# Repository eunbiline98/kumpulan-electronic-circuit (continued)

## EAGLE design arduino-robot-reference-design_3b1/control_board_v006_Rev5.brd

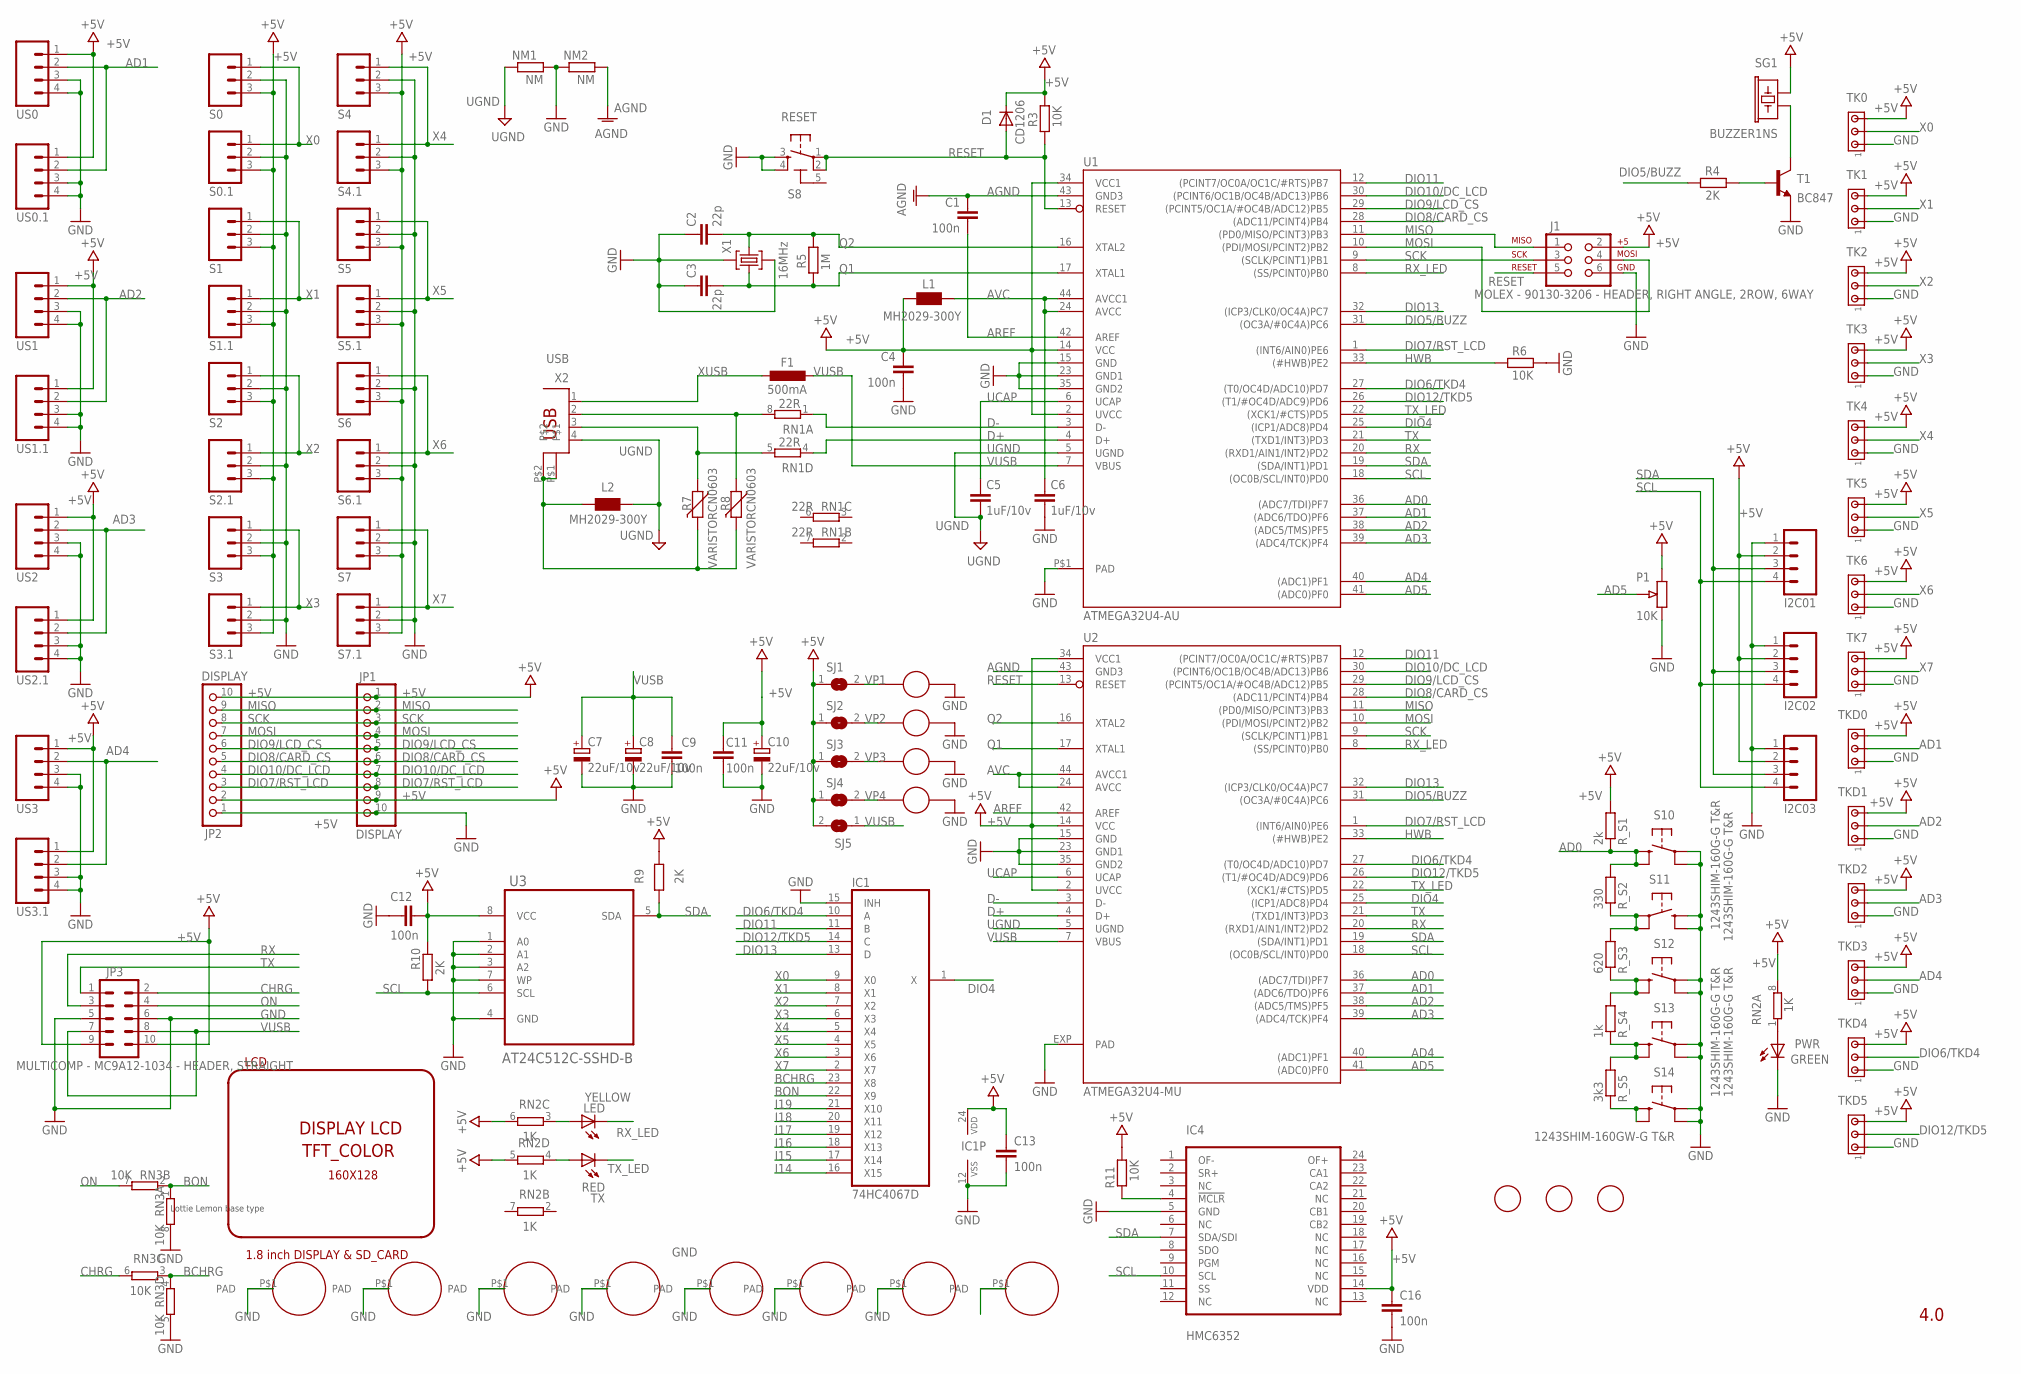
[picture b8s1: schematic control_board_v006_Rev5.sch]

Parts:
1, 2, 3: FIDUCIALMOUNT; FIDUCIA-MOUNT
C1, C4, C9, C11, C12, C13, C16: 100n; C0603-ROUND
C2, C3: 22p; C0603-ROUND
C5, C6: 1uF/10v; C0603-ROUND
C7, C8, C10: 22uF/10v; SMC_B
D1: CD1206; MINIMELF
F1: 500mA; L1812
G1: LOTTIE_LEMON_BASE_TYPE; BASE_ROBOT_001
H1, H2, H3, H4, H5, H6, H7, H8: 2.5-MOUNTING-HOLE; 2.5PAD
I2C01, I2C02, I2C03: M04PTH; 1X04
IC1: 74HC4067D; SO24W
IC4: HMC6352
J1: MOLEX - 90130-3206 - HEADER, RIGHT ANGLE, 2ROW, 6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; 2X3
JP1, JP2: DISPLAY; 1X10-TH
JP3: MULTICOMP - MC9A12-1034 - HEADER, STRAIGHT; 2X5-SHROUDED_LOCK
L1, L2: MH2029-300Y; 0805
LCD: 1.8 inch DISPLAY & SD_CARD; 1.8-LCD
LED: YELLOW; CHIP-LED0805
NM1, NM2: NM; R0805
P1: 10K; POT-V
PTZ1, PTZ2: LOTTIE_LEMON_PADS_SUP; PADS_LOTTIE_LEMON_SUP
PTZ3, PTZ4: LOTTIE_LEMON_PADS_SUP1; PADS_LOTTIE_LEMON_SUP
PWR: LEDCHIP-LED0805; CHIP-LED0805
R3, R6, R11: 10K; R0603-ROUND
R4, R9, R10: 2K; R0603-ROUND
R5: 1M; R0603-ROUND
R7, R8: VARISTORCN0603; CT/CN0603
RN1: 22R; CAY16
RN2: 1K; CAY16
RN3: 10K; CAY16
R_S1: 2k; R0603-ROUND
R_S2: 330; R0603-ROUND
R_S3: 620; R0603-ROUND
R_S4: 1k; R0603-ROUND
R_S5: 3k3; R0603-ROUND
S0, S0.1, S1, S1.1, S2, S2.1, S3, S3.1, S4, S4.1, S5, S5.1, S6, S6.1, S7, S7.1: M03PTH; 1X03
S8: RESET; TS42
S10, S11, S12, S13: 1243SHIM-160G-G T&R; TACTILE-SMD-12MM
S14: 1243SHIM-160GW-G T&R; TACTILE-SMD-12MM
SG1: BUZZER1NS; BUZZER-12MM-NS
SJ1, SJ2, SJ3, SJ4: SJ
SJ5: SJL
T1: BC847; SOT23
TK0, TK1, TK2, TK3, TK4, TK5, TK6, TK7: MTA03-100; 10X03MTA
TKD0, TKD1, TKD2, TKD3, TKD4, TKD5: MTA03-100; 10X03MTA
TX: RED; CHIP-LED0805
U1: ATMEGA32U4-AU; TQFP44-PAD
U2: ATMEGA32U4-MU; QFN44ML7X7
U3: AT24C512C-SSHD-B; SOIC127P600X175-8N
US0, US0.1, US1, US1.1, US2, US2.1, US3, US3.1: M04PTH; 1X04
X1: 16MHz; CRYSTAL-3.2-2.5
X2: USB; PN61729

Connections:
5-GND: S8.5 (5-GND)
+5V: C4.1, C10.+, C11.1, C12.1, C13.1, C16.1, D1.C, I2C01.2, I2C02.2, I2C03.2, IC1.24 (VDD), IC4.14 (VDD), J1.2, JP1.1, JP1.9, JP2.2, JP2.10, JP3.9, JP3.10, L1.2, P1.B, R3.1, R9.2, R10.1, R11.1, RN2.5 (2), RN2.6 (2), RN2.8 (2), R_S1.2, S0.3, S0.1.3, S1.3, S1.1.3, S2.3, S2.1.3, S3.3, S3.1.3, S4.3, S4.1.3, S5.3, S5.1.3, S6.3, S6.1.3, S7.3, S7.1.3, SG1.+ (1), SJ1.1, SJ2.1, SJ3.1, SJ4.1, SJ5.2, TK0.3, TK1.3, TK2.3, TK3.3, TK4.3, TK5.3, TK6.3, TK7.3, TKD0.3, TKD1.3, TKD2.3, TKD3.3, TKD4.3, TKD5.3, U1.2 (UVCC), U1.14 (VCC), U1.34 (VCC1), U2.2 (UVCC), U2.14 (VCC), U2.34 (VCC1), U3.8 (VCC), US0.1, US0.1.1, US1.1, US1.1.1, US2.1, US2.1.1, US3.1, US3.1.1
AD0: R_S1.1, R_S2.2, S10.P$3 (3), S10.P$4 (4), U1.36 ((ADC7/TDI)PF7), U2.36 ((ADC7/TDI)PF7)
AD1: TKD0.2, U1.37 ((ADC6/TDO)PF6), U2.37 ((ADC6/TDO)PF6), US0.2, US0.1.2
AD2: TKD1.2, U1.38 ((ADC5/TMS)PF5), U2.38 ((ADC5/TMS)PF5), US1.2, US1.1.2
AD3: TKD2.2, U1.39 ((ADC4/TCK)PF4), U2.39 ((ADC4/TCK)PF4), US2.2, US2.1.2
AD4: TKD3.2, U1.40 ((ADC1)PF1), U2.40 ((ADC1)PF1), US3.2, US3.1.2
AD5: P1.C, U1.41 ((ADC0)PF0), U2.41 ((ADC0)PF0)
AGND: C1.1, NM2.1, U1.43 (GND3), U2.43 (GND3)
AREF: C1.2, U1.42 (AREF), U2.42 (AREF)
AVC: C6.1, L1.1, U1.24 (AVCC), U1.44 (AVCC1), U2.24 (AVCC), U2.44 (AVCC1)
BCHRG: IC1.23 (X8), RN3.3 (1), RN3.4 (1)
BON: IC1.22 (X9), RN3.1, RN3.2 (1)
CHRG: JP3.2, RN3.6 (2)
D+: RN1.4 (1), U1.4 (D+), U2.4 (D+)
D-: RN1.1, U1.3 (D-), U2.3 (D-)
DIO4: IC1.1 (X), U1.25 ((ICP1/ADC8)PD4), U2.25 ((ICP1/ADC8)PD4)
DIO5/BUZZ: R4.2, U1.31 ((OC3A/#0C4A)PC6), U2.31 ((OC3A/#0C4A)PC6)
DIO6/TKD4: IC1.10 (A), TKD4.2, U1.27 ((T0/OC4D/ADC10)PD7), U2.27 ((T0/OC4D/ADC10)PD7)
DIO7/RST_LCD: JP1.8, JP2.3, U1.1 ((INT6/AIN0)PE6), U2.1 ((INT6/AIN0)PE6)
DIO8/CARD_CS: JP1.6, JP2.5, U1.28 ((ADC11/PCINT4)PB4), U2.28 ((ADC11/PCINT4)PB4)
DIO9/LCD_CS: JP1.5, JP2.6, U1.29 ((PCINT5/OC1A/#OC4B/ADC12)PB5), U2.29 ((PCINT5/OC1A/#OC4B/ADC12)PB5)
DIO10/DC_LCD: JP1.7, JP2.4, U1.30 ((PCINT6/OC1B/OC4B/ADC13)PB6), U2.30 ((PCINT6/OC1B/OC4B/ADC13)PB6)
DIO11: IC1.11 (B), U1.12 ((PCINT7/OC0A/OC1C/#RTS)PB7), U2.12 ((PCINT7/OC0A/OC1C/#RTS)PB7)
DIO12/TKD5: IC1.14 (C), TKD5.2, U1.26 ((T1/#OC4D/ADC9)PD6), U2.26 ((T1/#OC4D/ADC9)PD6)
DIO13: IC1.13 (D), U1.32 ((ICP3/CLK0/OC4A)PC7), U2.32 ((ICP3/CLK0/OC4A)PC7)
GND: C2.1, C3.1, C4.2, C6.2, C7.-, C8.-, C9.2, C10.-, C11.2, C12.2, C13.2, C16.2, H1.P$1, H2.P$1, H3.P$1, H4.P$1, H5.P$1, H6.P$1, H7.P$1, H8.P$1, I2C01.1, I2C02.1, I2C03.1, IC1.12 (VSS), IC1.15 (INH), IC4.5 (GND), J1.6, JP1.10, JP2.1, JP3.5, JP3.6, NM1.1, NM2.2, P1.A, PTZ1.P$52 (2), PTZ2.P$52 (2), PTZ3.P$52 (2), PTZ4.P$52 (2), PWR.C, R6.1, RN3.5 (2), RN3.8 (2), S0.2, S0.1.2, S1.2, S1.1.2, S2.2, S2.1.2, S3.2, S3.1.2, S4.2, S4.1.2, S5.2, S5.1.2, S6.2, S6.1.2, S7.2, S7.1.2, S8.3, S8.4, S10.P$1 (1), S10.P$2 (2), S11.P$3 (3), S11.P$4 (4), S12.P$1 (1), S12.P$2 (2), S13.P$1 (1), S13.P$2 (2), S14.P$1 (1), S14.P$2 (2), T1.2 (E), TK0.1, TK1.1, TK2.1, TK3.1, TK4.1, TK5.1, TK6.1, TK7.1, TKD0.1, TKD1.1, TKD2.1, TKD3.1, TKD4.1, TKD5.1, U1.15 (GND), U1.23 (GND1), U1.35 (GND2), U1.P$1 (PAD), U2.15 (GND), U2.23 (GND1), U2.35 (GND2), U2.EXP (PAD), U3.1 (A0), U3.2 (A1), U3.3 (A2), U3.4 (GND), U3.7 (WP), US0.3, US0.4, US0.1.3, US0.1.4, US1.3, US1.4, US1.1.3, US1.1.4, US2.3, US2.4, US2.1.3, US2.1.4, US3.3, US3.4, US3.1.3, US3.1.4, X1.2 (GND), X1.4 (GND)
HWB: R6.2, U1.33 ((#HWB)PE2), U2.33 ((#HWB)PE2)
I14: IC1.16 (X15)
I15: IC1.17 (X14)
I16: IC1.18 (X13)
I17: IC1.19 (X12)
I18: IC1.20 (X11)
I19: IC1.21 (X10)
MISO: J1.1, JP1.2, JP2.9, U1.11 ((PD0/MISO/PCINT3)PB3), U2.11 ((PD0/MISO/PCINT3)PB3)
MOSI: J1.4, JP1.4, JP2.7, U1.10 ((PDI/MOSI/PCINT2)PB2), U2.10 ((PDI/MOSI/PCINT2)PB2)
unnamed: R8.1, RN1.8 (2), X2.2
unnamed: R7.1, RN1.5 (2), X2.3
unnamed: RN2.4 (1), TX.A
unnamed: IC4.4 (!MCLR), R11.2
unnamed: L2.1, R7.2, R8.2, X2.P$1, X2.P$2
unnamed: R_S2.1, R_S3.2, S11.P$1 (1), S11.P$2 (2)
unnamed: LED.A, RN2.3 (1)
unnamed: SG1.- (2), T1.3 (C)
unnamed: PWR.A, RN2.1
unnamed: R_S3.1, R_S4.2, S12.P$3 (3), S12.P$4 (4)
unnamed: R_S4.1, R_S5.2, S13.P$3 (3), S13.P$4 (4)
unnamed: R_S5.1, S14.P$3 (3), S14.P$4 (4)
unnamed: R4.1, T1.1 (B)
ON: JP3.4, RN3.7 (2)
Q1: C3.2, R5.2, U1.17 (XTAL1), U2.17 (XTAL1), X1.1 (C1)
Q2: C2.2, R5.1, U1.16 (XTAL2), U2.16 (XTAL2), X1.3 (C2)
RESET: D1.A, J1.5, R3.2, S8.1, S8.2, U1.13 (RESET), U2.13 (RESET)
RX: JP3.3, U1.20 ((RXD1/AIN1/INT2)PD2), U2.20 ((RXD1/AIN1/INT2)PD2)
RX_LED: LED.C, U1.8 ((SS/PCINT0)PB0), U2.8 ((SS/PCINT0)PB0)
SCK: J1.3, JP1.3, JP2.8, U1.9 ((SCLK/PCINT1)PB1), U2.9 ((SCLK/PCINT1)PB1)
SCL: I2C01.4, I2C02.4, I2C03.4, IC4.10 (SCL), R10.2, U1.18 ((OC0B/SCL/INT0)PD0), U2.18 ((OC0B/SCL/INT0)PD0), U3.6 (SCL)
SDA: I2C01.3, I2C02.3, I2C03.3, IC4.7 (SDA/SDI), R9.1, U1.19 ((SDA/INT1)PD1), U2.19 ((SDA/INT1)PD1), U3.5 (SDA)
TX: JP3.1, U1.21 ((TXD1/INT3)PD3), U2.21 ((TXD1/INT3)PD3)
TX_LED: TX.C, U1.22 ((XCK1/#CTS)PD5), U2.22 ((XCK1/#CTS)PD5)
UCAP: C5.1, U1.6 (UCAP), U2.6 (UCAP)
UGND: C5.2, L2.2, NM1.2, U1.5 (UGND), U2.5 (UGND), X2.4
VP1: PTZ3.P$42 (1), SJ1.2
VP2: PTZ4.P$42 (1), SJ2.2
VP3: PTZ1.P$42 (1), SJ3.2
VP4: PTZ2.P$42 (1), SJ4.2
VUSB: C7.+, C8.+, C9.1, F1.2, JP3.7, JP3.8, SJ5.1, U1.7 (VBUS), U2.7 (VBUS)
X0: IC1.9 (X0), S0.1, S0.1.1, TK0.2
X1: IC1.8 (X1), S1.1, S1.1.1, TK1.2
X2: IC1.7 (X2), S2.1, S2.1.1, TK2.2
X3: IC1.6 (X3), S3.1, S3.1.1, TK3.2
X4: IC1.5 (X4), S4.1, S4.1.1, TK4.2
X5: IC1.4 (X5), S5.1, S5.1.1, TK5.2
X6: IC1.3 (X6), S6.1, S6.1.1, TK6.2
X7: IC1.2 (X7), S7.1, S7.1.1, TK7.2
XUSB: F1.1, X2.1

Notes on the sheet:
GREEN
4.0

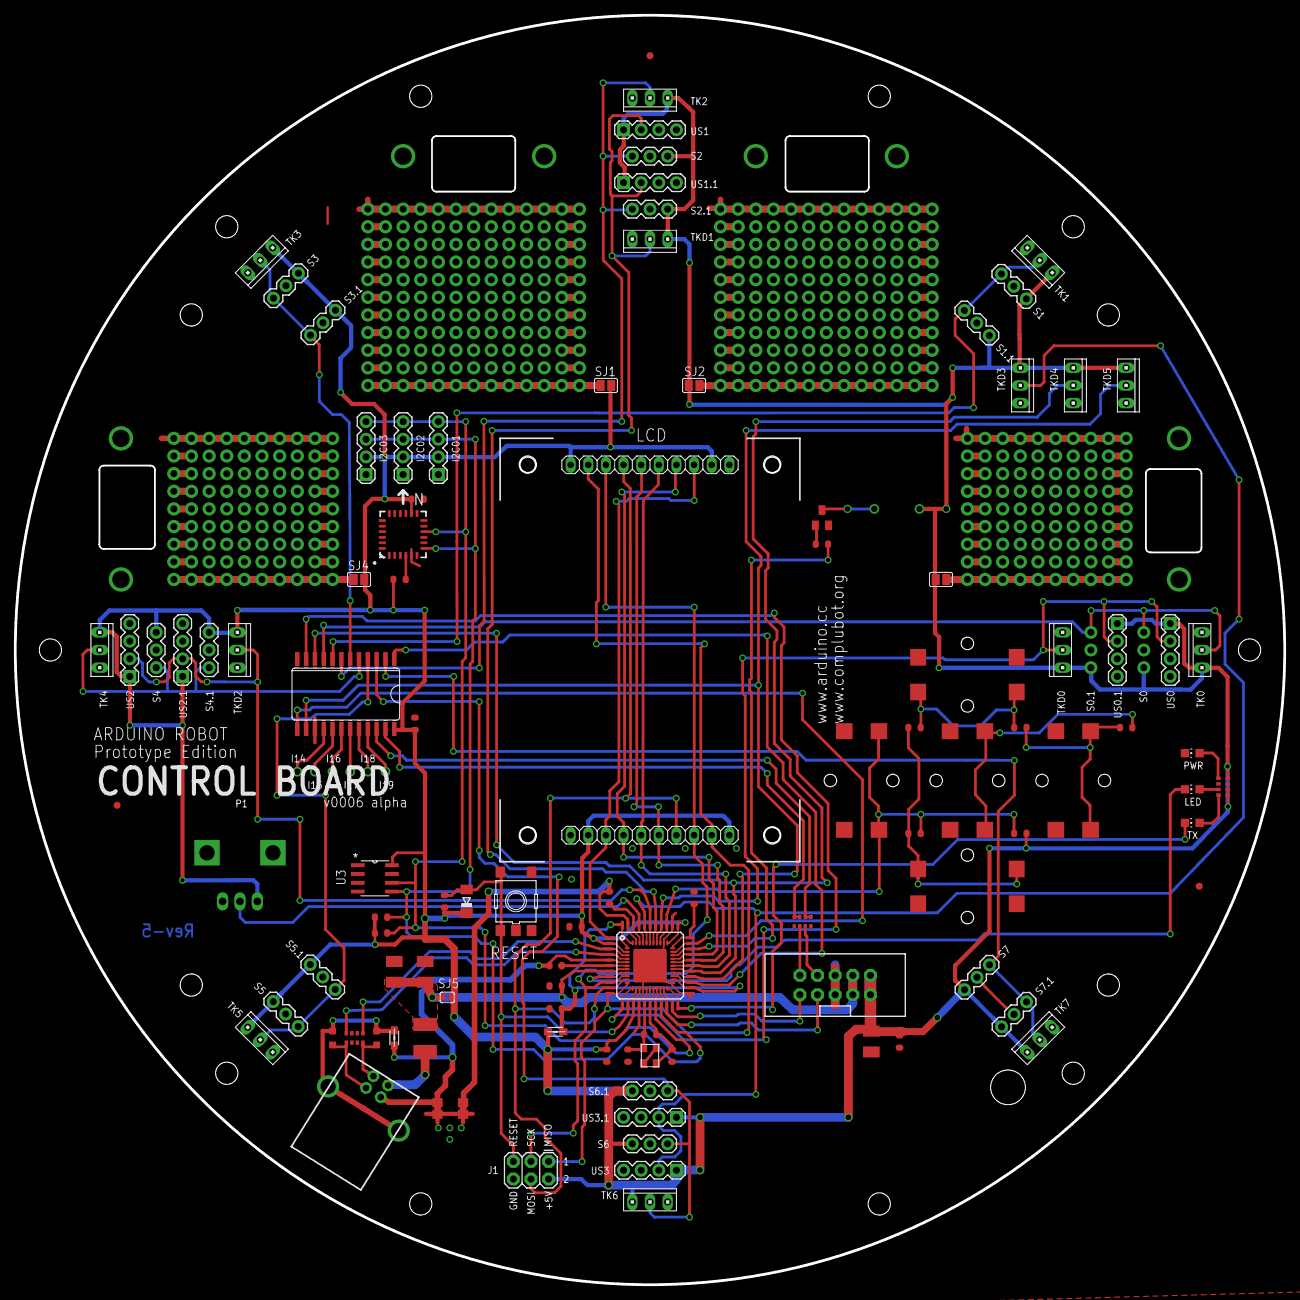
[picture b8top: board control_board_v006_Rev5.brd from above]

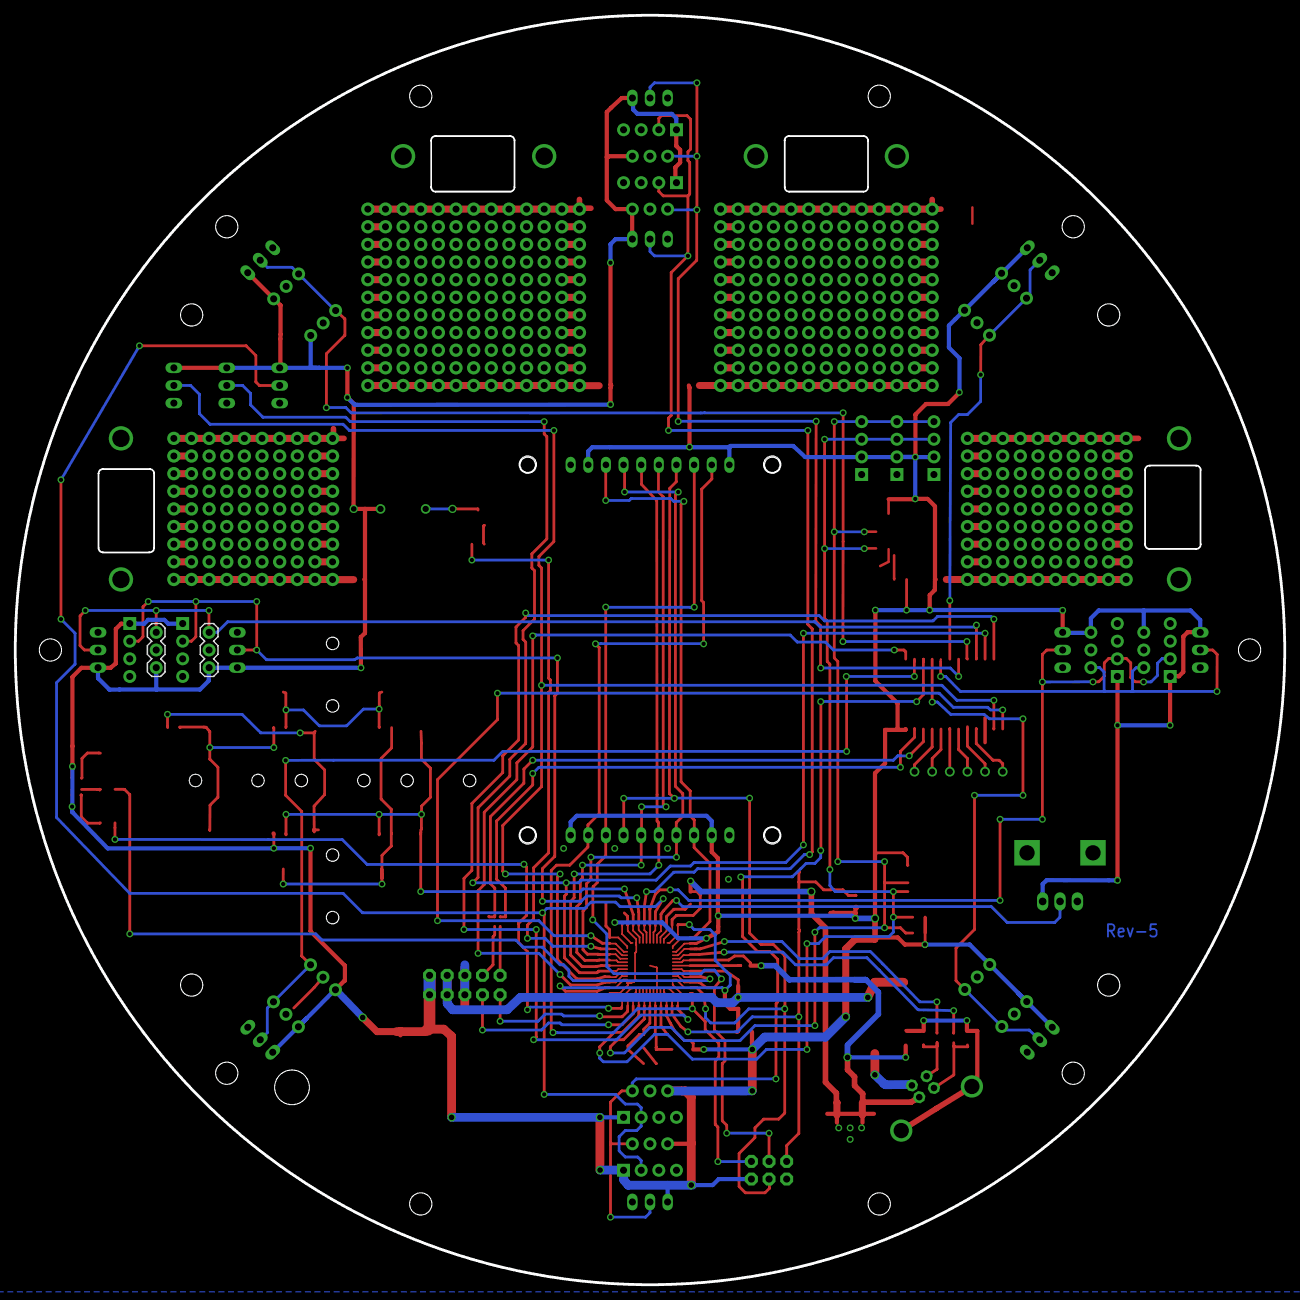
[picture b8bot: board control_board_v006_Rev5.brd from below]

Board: 2 copper layers, 182.9 x 182.9 mm, 123 parts (2 on the bottom side), 69 nets.

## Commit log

2019-05-08 kumpulan-electronic-circuit
